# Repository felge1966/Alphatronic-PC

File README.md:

# Alphatronic-PC
Module und Zubehör zum PC-8

https://forum.classic-computing.de/forum/index.php?thread/22451-ta-pc-8-dies-und-das/

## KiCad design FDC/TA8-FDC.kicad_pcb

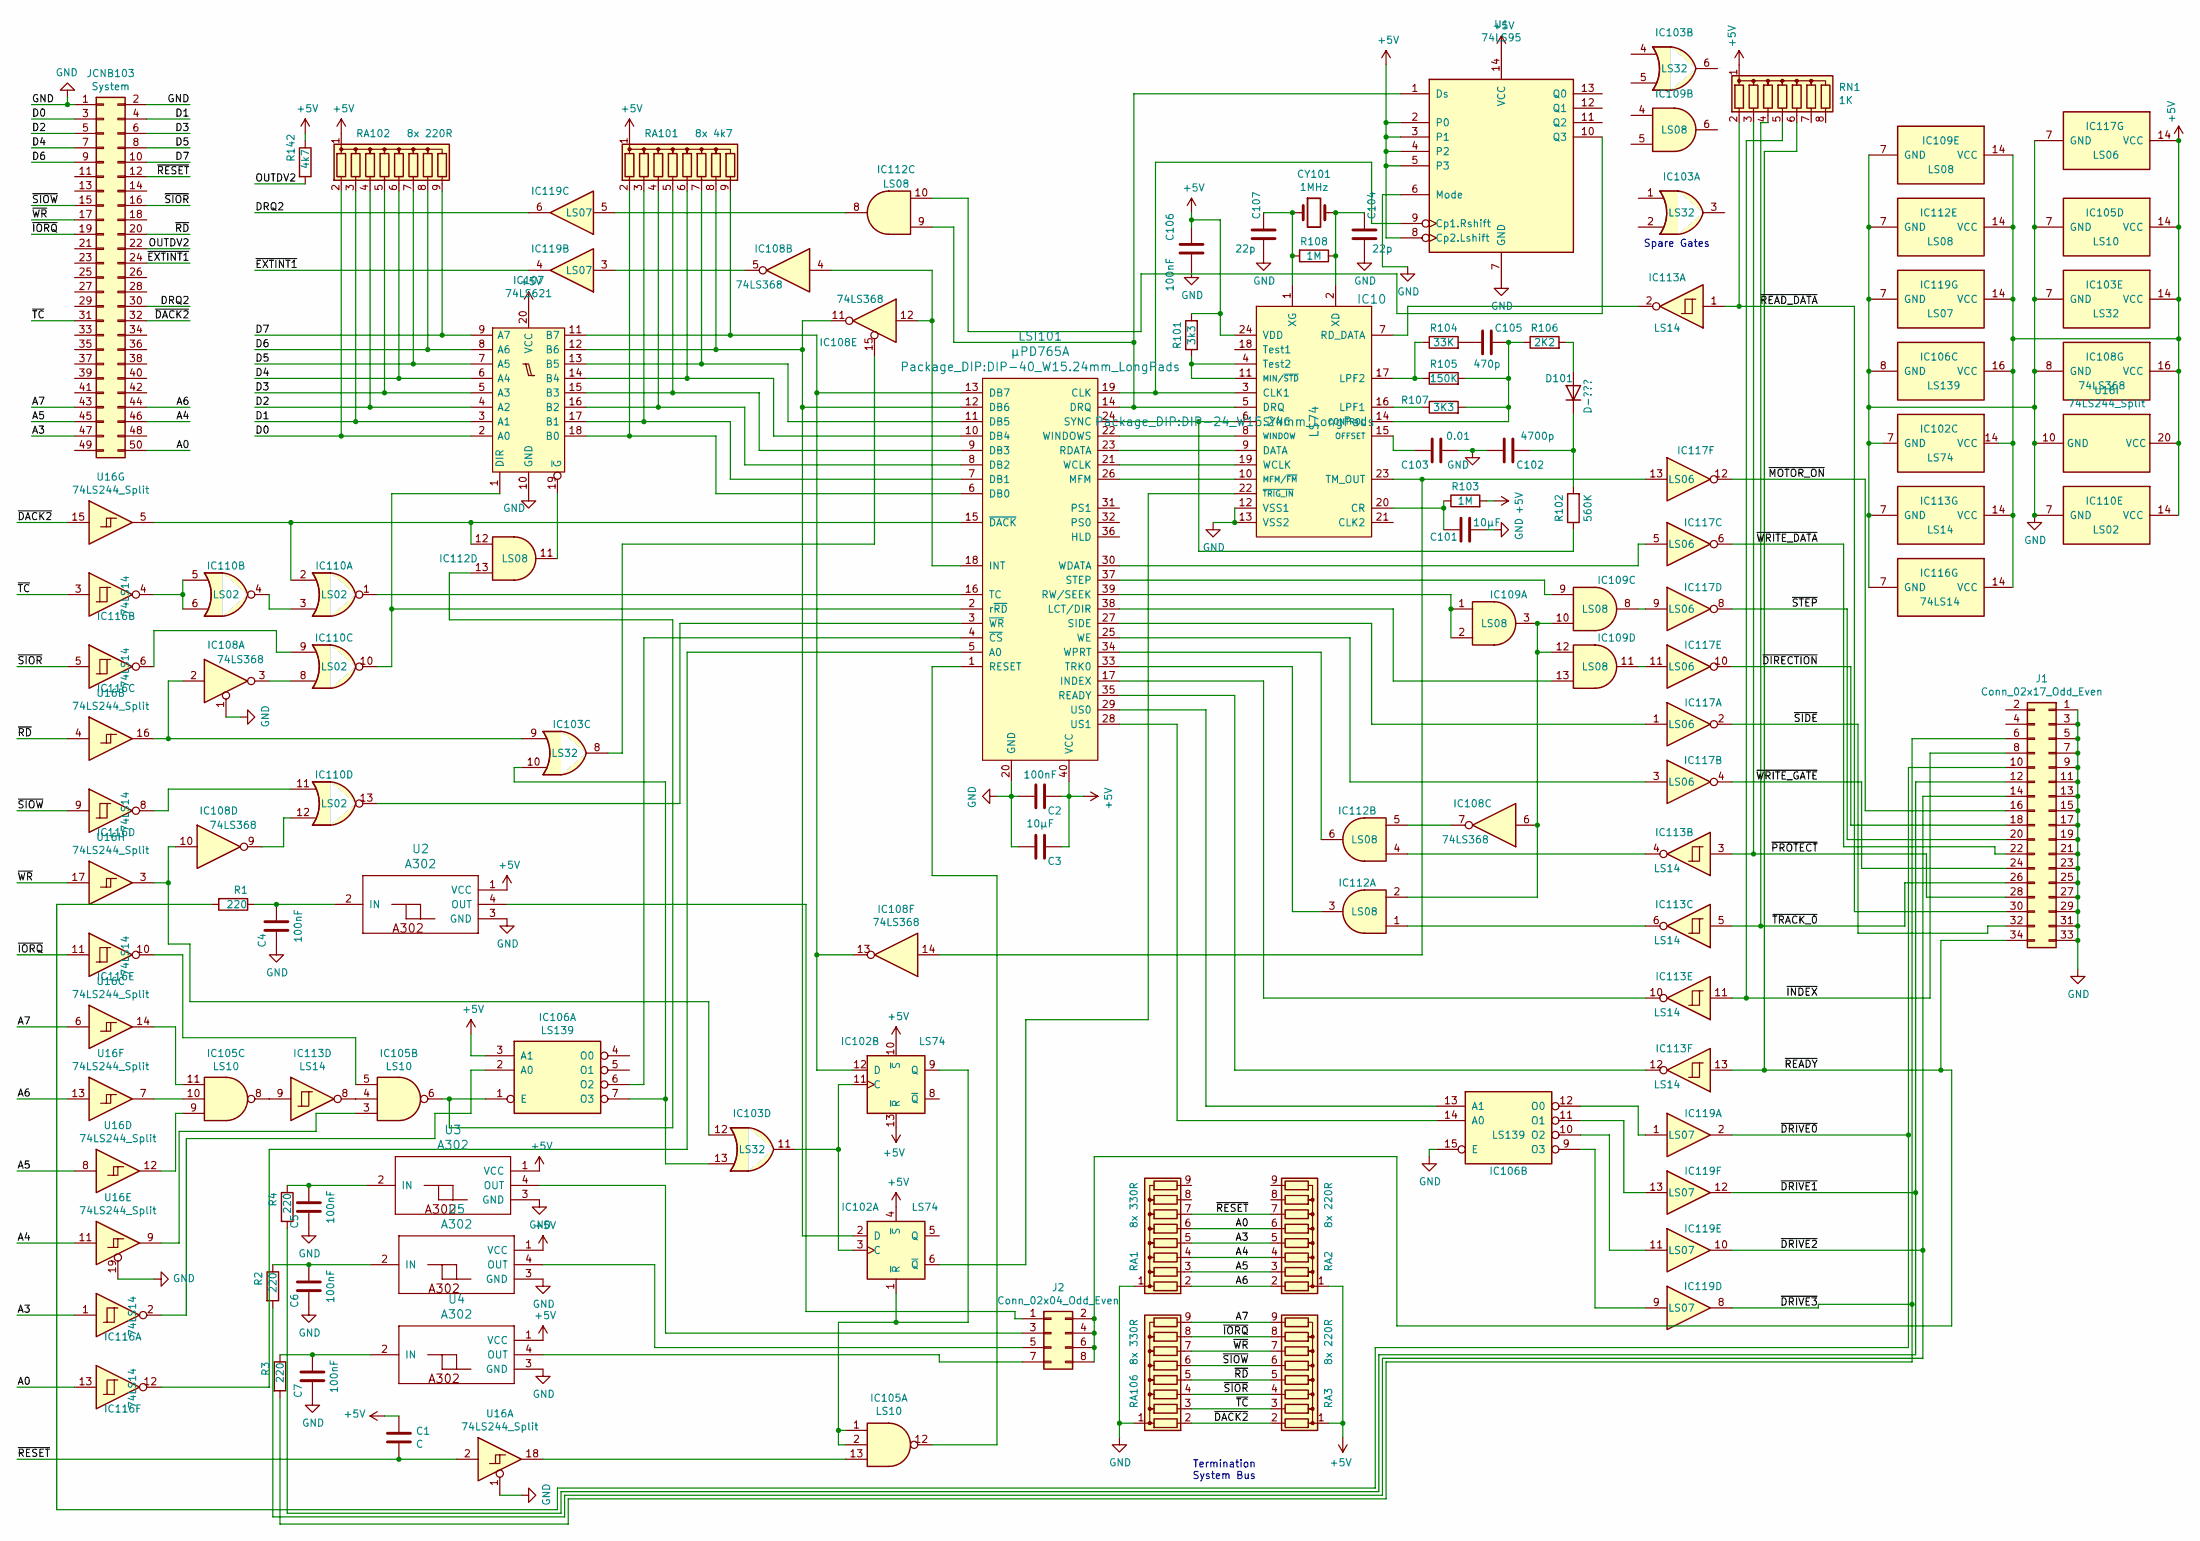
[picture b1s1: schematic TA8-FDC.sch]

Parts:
C1: C; CP_Radial_D4.0mm_P2.00mm
C2, C4, C5, C6, C7, C106: 100nF; C_Disc_D3.0mm_W2.0mm_P2.50mm
C3, C101: 10µF; CP_Radial_D4.0mm_P2.00mm
C102: 4700p; C_Disc_D3.0mm_W2.0mm_P2.50mm
C103: 0.01; C_Disc_D3.0mm_W2.0mm_P2.50mm
C104, C107: 22p; C_Disc_D3.0mm_W2.0mm_P2.50mm
C105: 470p; C_Disc_D3.0mm_W2.0mm_P2.50mm
CY101: 1MHz; Crystal_HC49-4H_Vertical
D101: D-???; D_DO-15_P10.16mm_Horizontal
IC10: LS74; DIP-24_W15.24mm_LongPads
IC102: LS74; DIP-14_W7.62mm_LongPads
IC103: LS32; DIP-14_W7.62mm_LongPads
IC105: LS10; DIP-14_W7.62mm_LongPads
IC106: LS139; DIP-16_W7.62mm_LongPads
IC107: 74LS621; DIP-20_W7.62mm_LongPads
IC108: 74LS368; DIP-16_W7.62mm_LongPads
IC109, IC112: LS08; DIP-14_W7.62mm_LongPads
IC110: LS02; DIP-14_W7.62mm_LongPads
IC113: LS14; DIP-14_W7.62mm_LongPads
IC116: 74LS14; DIP-14_W7.62mm_LongPads
IC117: LS06; DIP-14_W7.62mm_LongPads
IC119: LS07; DIP-14_W7.62mm_LongPads
J1: Conn_02x17_Odd_Even; PinSocket_2x17_P2.54mm_Vertical
J2: Conn_02x04_Odd_Even; PinSocket_2x04_P2.54mm_Vertical
JCNB103: System; PinSocket_2x25_P2.54mm_Horizontal
LSI101: µPD765A; DIP-40_W15.24mm_LongPads
R1, R2, R3, R4: 220; R_Axial_DIN0207_L6.3mm_D2.5mm_P10.16mm_Horizontal
R101: 3k3; R_Axial_DIN0207_L6.3mm_D2.5mm_P10.16mm_Horizontal
R102: 560K; R_Axial_DIN0207_L6.3mm_D2.5mm_P10.16mm_Horizontal
R103, R108: 1M; R_Axial_DIN0207_L6.3mm_D2.5mm_P10.16mm_Horizontal
R104: 33K; R_Axial_DIN0207_L6.3mm_D2.5mm_P10.16mm_Horizontal
R105: 150K; R_Axial_DIN0207_L6.3mm_D2.5mm_P10.16mm_Horizontal
R106: 2K2; R_Axial_DIN0207_L6.3mm_D2.5mm_P10.16mm_Horizontal
R107: 3K3; R_Axial_DIN0207_L6.3mm_D2.5mm_P10.16mm_Horizontal
R142: 4k7; R_Axial_DIN0207_L6.3mm_D2.5mm_P10.16mm_Horizontal
RA1, RA106: 8x 330R; R_Array_SIP9
RA2, RA3, RA102: 8x 220R; R_Array_SIP9
RA101: 8x 4k7; R_Array_SIP9
RN1: 1K; R_Array_SIP8
U1: 74LS95; DIP-14_W7.62mm_LongPads
U2, U3, U4, U5: A302; DIP-4_W7.62mm_LongPads
U16: 74LS244_Split; DIP-20_W7.62mm_LongPads

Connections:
+5V: C1.1, C2.1, C3.1, C106.1, IC10.24 (VDD), IC102.4 (~S), IC102.10 (~S), IC102.13 (~R), IC102.14 (VCC), IC103.14 (VCC), IC105.14 (VCC), IC106.3 (A1), IC106.16 (VCC), IC107.20 (VCC), IC108.16 (VCC), IC109.14 (VCC), IC110.14 (VCC), IC112.14 (VCC), IC113.14 (VCC), IC116.14 (VCC), IC117.14 (VCC), IC119.14 (VCC), LSI101.40 (VCC), R101.2, R103.2, R142.1, RA2.1 (common), RA3.1 (common), RA101.1 (common), RA102.1 (common), RN1.1 (common), U1.2 (P0), U1.3 (P1), U1.4 (P2), U1.5 (P3), U1.8 (Cp2.Lshift), U1.14 (VCC), U2.1 (VCC), U3.1 (VCC), U4.1 (VCC), U5.1 (VCC), U16.20 (VCC)
/A0: IC116.13, JCNB103.50, RA1.6 (R5), RA2.6 (R5)
/A3: IC116.1, JCNB103.47, RA1.5 (R4), RA2.5 (R4)
/A4: JCNB103.46, RA1.4 (R3), RA2.4 (R3), U16.11
/A5: JCNB103.45, RA1.3 (R2), RA2.3 (R2), U16.8
/A6: JCNB103.44, RA1.2 (R1), RA2.2 (R1), U16.13
/A7: JCNB103.43, RA3.9 (R8), RA106.9 (R8), U16.6
/D0: IC107.2 (A0), JCNB103.3, RA102.2 (R1)
/D1: IC107.3 (A1), JCNB103.4, RA102.3 (R2)
/D2: IC107.4 (A2), JCNB103.5, RA102.4 (R3)
/D3: IC107.5 (A3), JCNB103.6, RA102.5 (R4)
/D4: IC107.6 (A4), JCNB103.7, RA102.6 (R5)
/D5: IC107.7 (A5), JCNB103.8, RA102.7 (R6)
/D6: IC107.8 (A6), JCNB103.9, RA102.8 (R7)
/D7: IC107.9 (A7), JCNB103.10, RA102.9 (R8)
/DRQ2: IC119.6, JCNB103.30
/OUTDV2: JCNB103.22, R142.2
/~DACK2: JCNB103.32, RA3.2 (R1), RA106.2 (R1), U16.15
/~DIRECTION: IC117.10, J1.18
/~DRIVE0: IC119.2, J1.10, R1.2
/~DRIVE1: IC119.12, J1.12, R4.2
/~DRIVE2: IC119.10, J1.14, R2.2
/~DRIVE3: IC119.8, J1.6, R3.2
/~EXTINT1: IC119.4, JCNB103.24
/~INDEX: IC113.11, J1.8, RN1.5 (R4)
/~IORQ: IC116.11, JCNB103.19, RA3.8 (R7), RA106.8 (R7)
/~MOTOR_ON: IC117.12, J1.16
/~PROTECT: IC113.3, J1.28, RN1.3 (R2)
/~RD: JCNB103.20, RA3.5 (R4), RA106.5 (R4), U16.4
/~READY: IC113.13, J1.34, J2.2, J2.4, J2.6, J2.8, RN1.6 (R5)
/~READ_DATA: IC113.1, J1.30, RN1.2 (R1)
/~RESET: C1.2, JCNB103.12, RA1.7 (R6), RA2.7 (R6), U16.2
/~SIDE: IC117.2, J1.32
/~SIOR: IC116.5, JCNB103.16, RA3.4 (R3), RA106.4 (R3)
/~SIOW: IC116.9, JCNB103.15, RA3.6 (R5), RA106.6 (R5)
/~STEP: IC117.8, J1.20
/~TC: IC116.3, JCNB103.31, RA3.3 (R2), RA106.3 (R2)
/~TRACK_0: IC113.5, J1.26, RN1.4 (R3)
/~WR: JCNB103.17, RA3.7 (R6), RA106.7 (R6), U16.17
/~WRITE_DATA: IC117.6, J1.22
/~WRITE_GATE: IC117.4, J1.24
GND: C2.2, C3.2, C4.1, C5.1, C6.1, C7.1, C101.2, C102.1, C103.2, C104.2, C106.2, C107.2, IC10.12 (VSS1), IC10.13 (VSS2), IC102.7 (GND), IC103.7 (GND), IC105.7 (GND), IC106.8 (GND), IC106.15 (E), IC107.10 (GND), IC108.1, IC108.8 (GND), IC109.7 (GND), IC110.7 (GND), IC112.7 (GND), IC113.7 (GND), IC116.7 (GND), IC117.7 (GND), IC119.7 (GND), J1.1, J1.3, J1.5, J1.7, J1.9, J1.11, J1.13, J1.15, J1.17, J1.19, J1.21, J1.23, J1.25, J1.27, J1.29, J1.31, J1.33, JCNB103.1, JCNB103.2, LSI101.20 (GND), RA1.1 (common), RA106.1 (common), U1.6 (Mode), U1.7 (GND), U2.3 (GND), U3.3 (GND), U4.3 (GND), U5.3 (GND), U16.1, U16.10 (GND), U16.19
unnamed: C4.2, R1.1, U2.2 (IN)
unnamed: C5.2, R4.1, U3.2 (IN)
unnamed: C6.2, R2.1, U5.2 (IN)
unnamed: C7.2, R3.1, U4.2 (IN)
unnamed: C101.1, IC10.20 (CR), R103.1
unnamed: C102.2, D101.1 (K), R102.2
unnamed: C103.1, IC10.15 (OFFSET)
unnamed: C104.1, CY101.2, IC10.2 (XD), R108.1
unnamed: C105.1, R104.2
unnamed: C105.2, IC10.14 (CONTROL), R105.2, R106.1, R107.2
unnamed: C107.1, CY101.1, IC10.1 (XG), R108.2
unnamed: D101.2 (A), R106.2
unnamed: IC10.3 (CLK1), LSI101.19 (CLK), U1.9 (Cp1.Rshift)
unnamed: IC10.5 (DRQ), IC112.9, LSI101.14 (DRQ), U1.1 (Ds)
unnamed: IC10.6 (SYNC), LSI101.24 (SYNC), R102.1
unnamed: IC10.7 (RD_DATA), IC113.2
unnamed: IC10.8 (WINDOW), LSI101.22 (WINDOWS)
unnamed: IC10.9 (DATA), LSI101.23 (RDATA)
unnamed: IC10.10 (MFM/~FM), LSI101.26 (MFM)
unnamed: IC10.4 (Test2), IC10.11 (MIN/~STD), R101.1
unnamed: IC10.16 (LPF1), R107.1
unnamed: IC10.17 (LPF2), R104.1, R105.1
unnamed: IC10.19 (WCLK), LSI101.21 (WCLK)
unnamed: IC10.22 (~TRIG_IN), IC102.6 (~Q)
unnamed: IC10.23 (TM_OUT), IC108.14, IC117.13
unnamed: IC102.1 (~R), IC102.9 (Q), IC105.1, IC105.2
unnamed: IC102.2 (D), IC107.12 (B6), IC108.11, LSI101.12 (DB6), RA101.8 (R7)
unnamed: IC102.3 (C), IC102.11 (C), IC103.11
unnamed: IC102.12 (D), IC107.11 (B7), IC108.13, LSI101.13 (DB7), RA101.9 (R8)
unnamed: IC103.8, IC108.15
unnamed: IC103.9, IC108.2, U16.16
unnamed: IC103.10, IC103.13, IC106.7 (O3)
unnamed: IC103.12, IC108.10, U16.3
unnamed: IC105.3, U16.9
unnamed: IC105.4, IC113.8
unnamed: IC105.5, IC116.10
unnamed: IC105.6, IC106.1 (E), IC112.13
unnamed: IC105.8, IC113.9
unnamed: IC105.9, U16.12
unnamed: IC105.10, U16.7
unnamed: IC105.11, U16.14
unnamed: IC105.12, LSI101.1 (RESET)
unnamed: IC105.13, U16.18
unnamed: IC106.2 (A0), IC116.2
unnamed: IC106.6 (O2), LSI101.4 (~CS)
unnamed: IC106.9 (O3), IC119.9
unnamed: IC106.10 (O2), IC119.11
unnamed: IC106.11 (O1), IC119.13
unnamed: IC106.12 (O0), IC119.1
unnamed: IC106.13 (A1), LSI101.29 (US0)
unnamed: IC106.14 (A0), LSI101.28 (US1)
unnamed: IC107.1 (DIR), IC110.10, LSI101.2 (r~RD)
unnamed: IC107.13 (B5), LSI101.11 (DB5), RA101.7 (R6)
unnamed: IC107.14 (B4), LSI101.10 (DB4), RA101.6 (R5)
unnamed: IC107.15 (B3), LSI101.9 (DB3), RA101.5 (R4)
unnamed: IC107.16 (B2), LSI101.8 (DB2), RA101.4 (R3)
unnamed: IC107.17 (B1), LSI101.7 (DB1), RA101.3 (R2)
unnamed: IC107.18 (B0), LSI101.6 (DB0), RA101.2 (R1)
unnamed: IC107.19 (~G), IC112.11
unnamed: IC108.3, IC110.8
unnamed: IC108.5, IC119.3
unnamed: IC108.6, IC109.3, IC109.10, IC109.12, IC112.2
unnamed: IC108.7, IC112.5
unnamed: IC108.9, IC110.12
unnamed: IC108.4, IC108.12, LSI101.18 (INT)
unnamed: IC109.1, IC109.2, LSI101.39 (RW/SEEK)
unnamed: IC109.8, IC117.9
unnamed: IC109.9, LSI101.37 (STEP)
unnamed: IC109.11, IC117.11
unnamed: IC109.13, LSI101.38 (LCT/DIR)
unnamed: IC110.1, LSI101.16 (TC)
unnamed: IC110.2, IC112.12, LSI101.15 (~DACK), U16.5
unnamed: IC110.3, IC110.4
unnamed: IC110.5, IC110.6, IC116.4
unnamed: IC110.9, IC116.6
unnamed: IC110.11, IC116.8
unnamed: IC110.13, LSI101.3 (~WR)
unnamed: IC112.1, IC113.6
unnamed: IC112.3, LSI101.33 (TRK0)
unnamed: IC112.4, IC113.4
unnamed: IC112.6, LSI101.34 (WPRT)
unnamed: IC112.8, IC119.5
unnamed: IC112.10, U1.10 (Q3)
unnamed: IC113.10, LSI101.17 (INDEX)
unnamed: IC113.12, LSI101.35 (READY)
unnamed: IC116.12, LSI101.5 (A0)
unnamed: IC117.1, LSI101.27 (SIDE)
unnamed: IC117.3, LSI101.25 (WE)
unnamed: IC117.5, LSI101.30 (WDATA)
unnamed: J2.1, U2.4 (OUT)
unnamed: J2.3, U3.4 (OUT)
unnamed: J2.5, U5.4 (OUT)
unnamed: J2.7, U4.4 (OUT)

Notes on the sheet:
Spare Gates
Termination System Bus

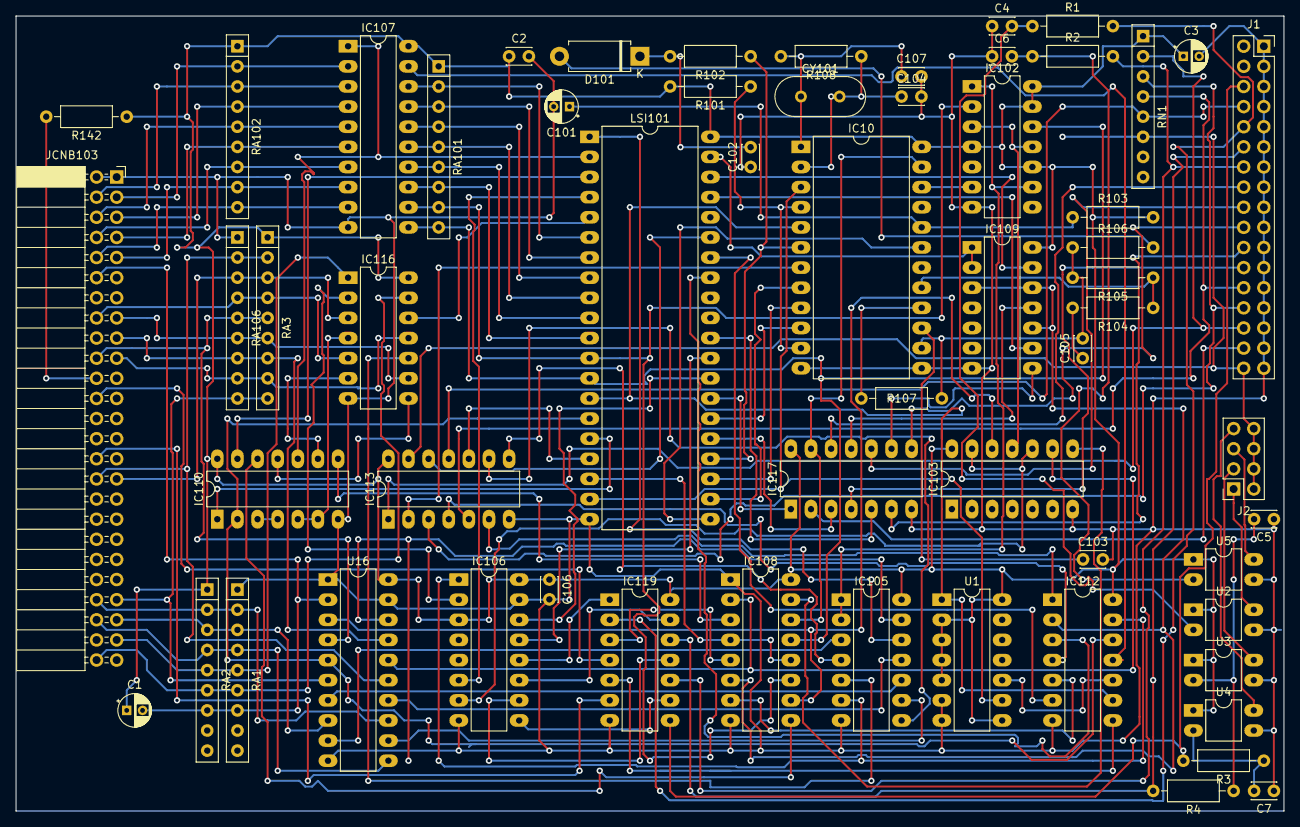
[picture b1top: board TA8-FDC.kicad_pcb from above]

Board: 2 copper layers, 160.0 x 100.3 mm, 60 parts (0 on the bottom side), 135 nets.
